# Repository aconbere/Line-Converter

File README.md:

# Line-Converter

A simple audio line output converter for JAMMA boards. Takes the amplified audio from a JAMMA board and brings them down to consumer audio levels for headphones or your own amplifier. Compatible with either mono or stereo board designs (switchable). Inputs on a block terminal for ease of use, outputs run to a 3.5mm jack.

## Voltage Divider

JAMMA boards will typically output audio at roughly +/- 6V peak to peak, the goal of this board is to reduce that to 0.5V peak to peak expected for standard audio equipment. This board uses a voltage divider bridge with Z1 = 390 Ohms and Z2 = 47 ohms for a ratio of 0.1.

## Isolation

The board also isolates the board from the downstream audio equipment by way of two 1-1 transformers. These are in place to prevent failures in the board cascading to downstream equipement.

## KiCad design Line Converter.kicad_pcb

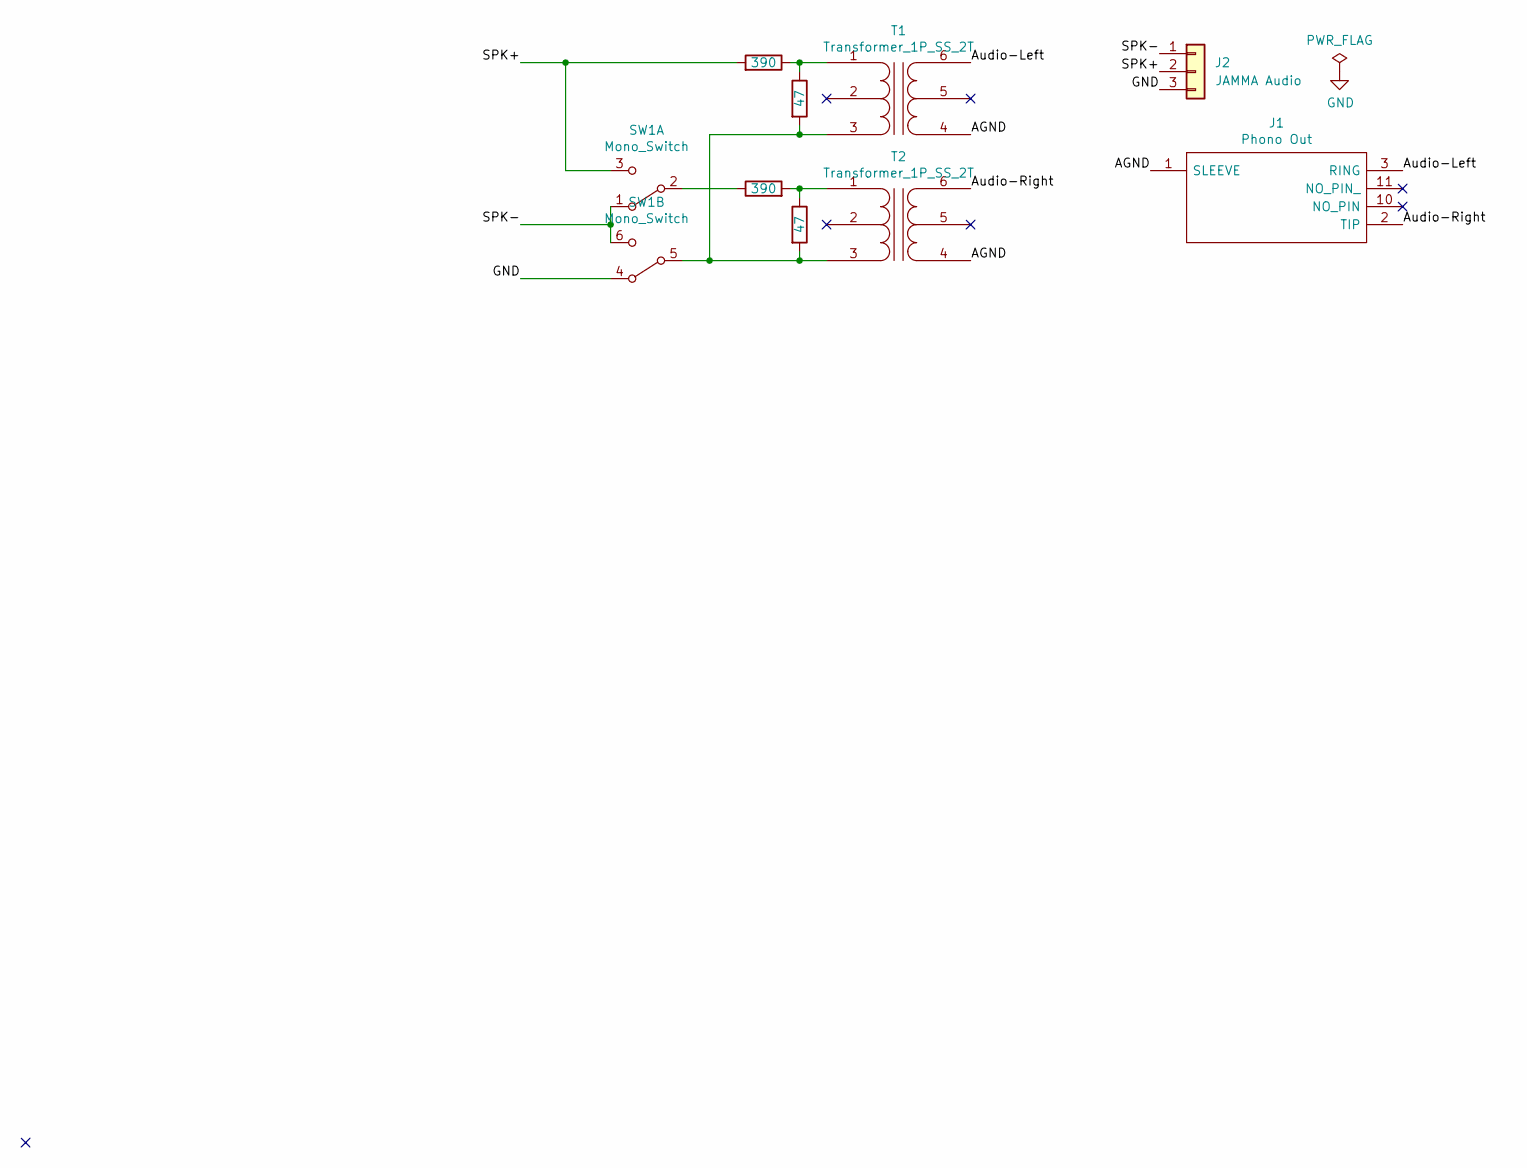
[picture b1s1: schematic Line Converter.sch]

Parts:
J1: Phono Out; SJ13523N; Mouser Part Number 490-SJ1-3523N
J2: JAMMA Audio; SHDR3W100P0X500_1X3_1500X900X1290P
R10, R11: 390; R_Axial_DIN0204_L3.6mm_D1.6mm_P5.08mm_Horizontal
R12, R13: 47; R_Axial_DIN0204_L3.6mm_D1.6mm_P5.08mm_Horizontal
SW1: Mono_Switch; 400UDP1R1BLKM2RE
T1, T2: Transformer_1P_SS_2T; TY145P

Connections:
/AGND: J1.1 (SLEEVE), T1.4 (SA), T2.4 (SA)
/Audio-Left: J1.3 (RING), T1.6 (SB)
/Audio-Right: J1.2 (TIP), T2.6 (SB)
/SPK+: J2.2, R10.2, SW1.3 (C)
/SPK-: J2.1, SW1.1 (A), SW1.6 (C)
GND: J2.3, SW1.4 (A)
unnamed: R10.1, R12.1, T1.1 (AA)
unnamed: R11.1, SW1.2 (B)
unnamed: R11.2, R13.1, T2.1 (AA)
unnamed: R12.2, R13.2, SW1.5 (B), T1.3 (AB), T2.3 (AB)

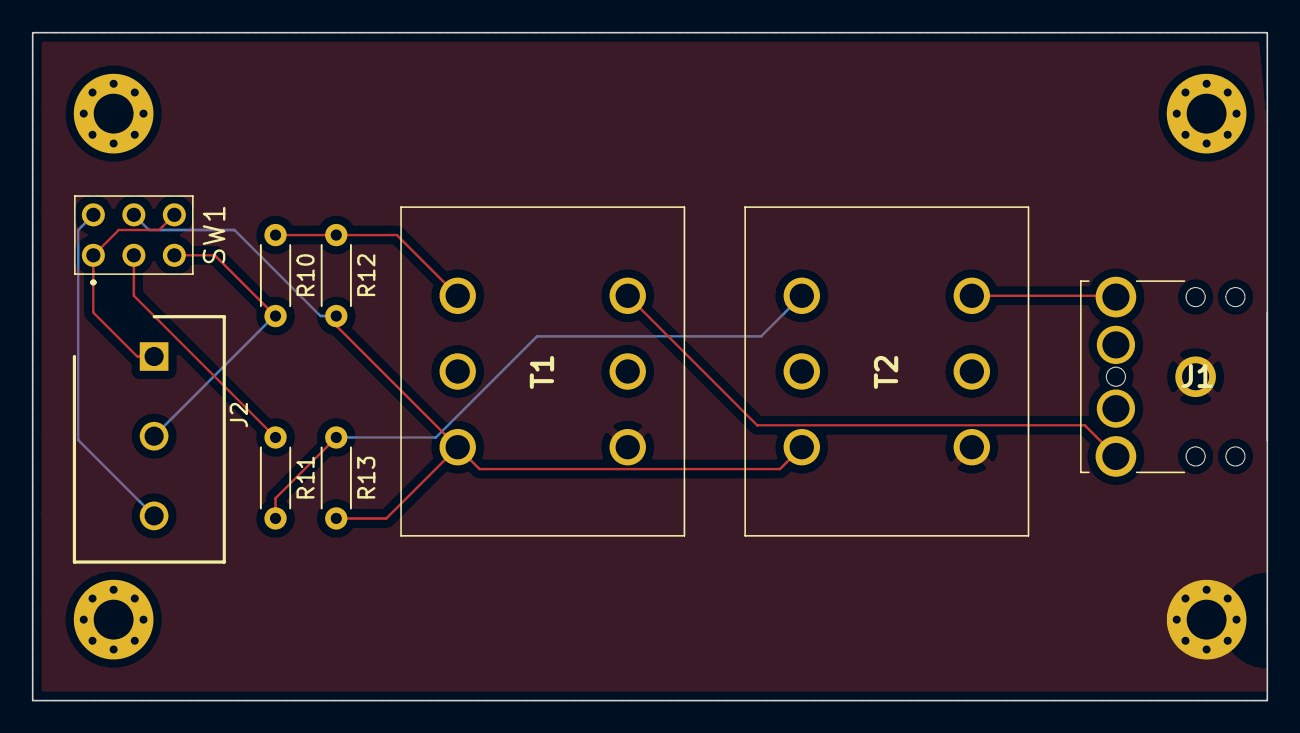
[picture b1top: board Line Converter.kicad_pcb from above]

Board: 2 copper layers, 77.5 x 41.9 mm, 9 parts (0 on the bottom side), 10 nets.

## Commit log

2020-06-20 add gitignore
2020-07-31 don't remember :)
2020-08-03 Add readme description
